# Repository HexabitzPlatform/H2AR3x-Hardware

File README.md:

# H2AR3x-Hardware
Hexabitz AC Current and Voltage Sensor Module Hardware Design

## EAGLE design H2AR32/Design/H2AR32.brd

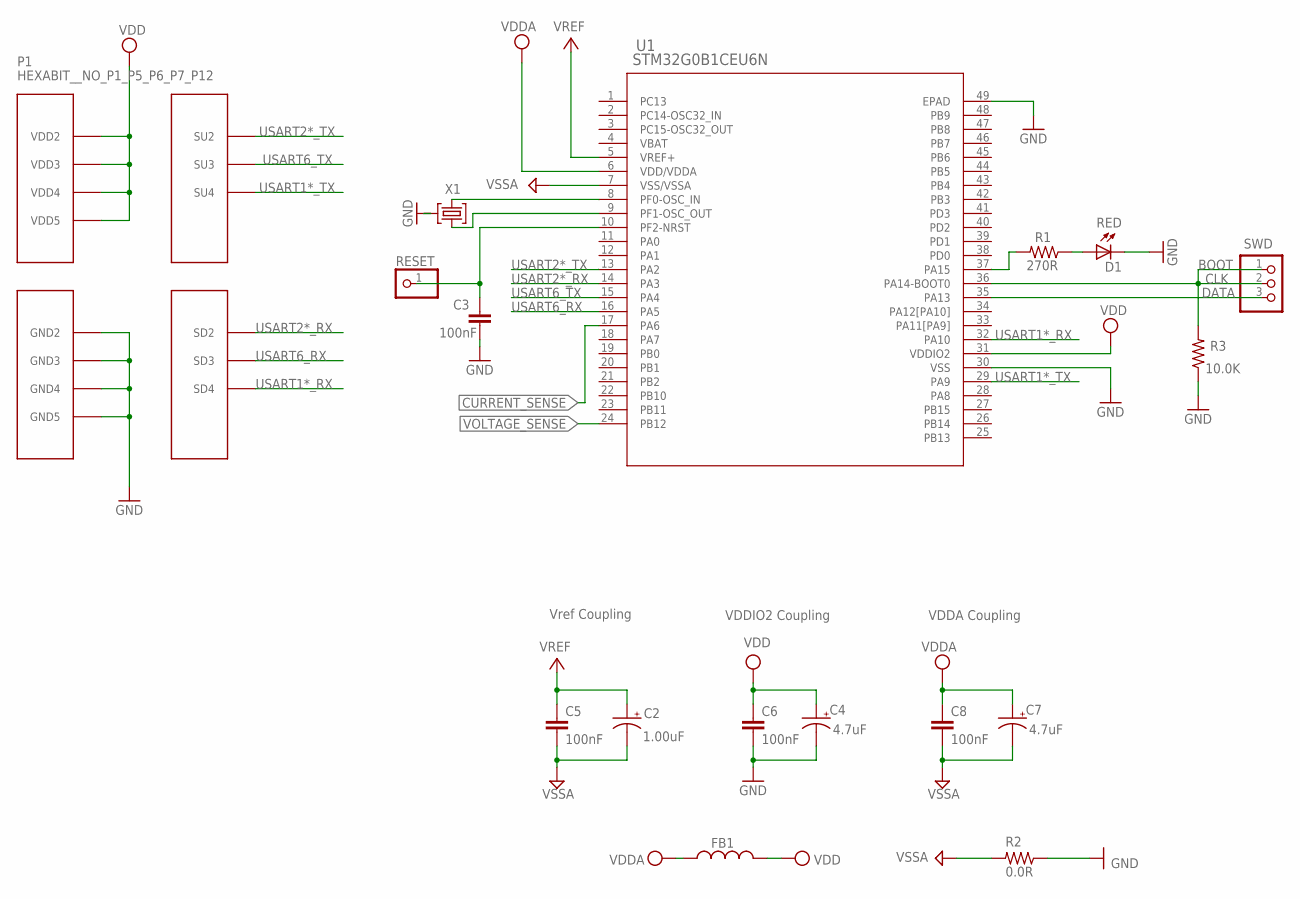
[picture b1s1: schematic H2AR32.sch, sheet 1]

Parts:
C2: 1.00uF; C-0805-POL; TOLERANCE 10%; VOLTAGE_RATING 16V; MPN CC0805KKX7R7BB105
C3, C5, C6: 100nF; C-0603; TOLERANCE 10%; VOLTAGE_RATING 10V; MPN C0603C104K8RACTU
C4, C7: 4.7uF; C-0805-POL; TOLERANCE 10%; VOLTAGE_RATING 25V; MPN GRM21BC81E475KA12L
C8: 100nF; C-0603; TOLERANCE 10%; VOLTAGE_RATING 10; MPN C0603C104K8RACTU
D1: RED; VLMS1300-GS08; MPN VLMS1300-GS08
FB1: FB-TDK_MMZ1608Y300B; MPN MMZ1608Y300B
P1: HEXABIT__NO_P1_P5_P6_P7_P12; HEXABIT_17.32_NO_P1_P6_P5_P7_P12
R1: 270R; R-0603; TOLERANCE 5%; MPN RC0603FR-07270RL
R2: 0.0R; R-0603; MPN RC0603JR-070RL
R3: 10.0K; R-0603; TOLERANCE 5%; MPN RC0603JR-0710KL
RESET: R; 1X01
SWD: PINHD-1X3; 1X03
U1: STM32G0B1CEU6N; HEXABITZ_ICS_QFN_B1CEU6_STM-L
X1: XTALL_CSTCE8M00G52

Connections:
CLK: R3.2, SWD.1, SWD.2, U1.36 (PA14-BOOT0)
CURRENT_SENSE: U1.17 (PA6); also elsewhere on the board
DATA: SWD.3, U1.35 (PA13)
GND: C3.2, C4.2 (-), C6.2, D1.C, P1.PAD_PD8 (GND2), P1.PAD_PD9 (GND3), P1.PAD_PD10 (GND4), P1.PAD_PD11 (GND5), R2.1, R3.1, U1.30 (VSS), U1.49 (EPAD), X1.P$2 (2)
unnamed: R1.2, U1.37 (PA15)
unnamed: D1.A, R1.1
unnamed: U1.8 (PF0-OSC_IN), X1.P$1 (1)
unnamed: U1.9 (PF1-OSC_OUT), X1.P$3 (3)
unnamed: C3.1, RESET.1, U1.10 (PF2-NRST)
USART1*_RX: P1.PAD_PD4 (SD4), U1.32 (PA10)
USART1*_TX: P1.PAD_PU4 (SU4), U1.29 (PA9)
USART2*_RX: P1.PAD_PD2 (SD2), U1.14 (PA3)
USART2*_TX: P1.PAD_PU2 (SU2), U1.13 (PA2)
USART6_RX: P1.PAD_PD3 (SD3), U1.16 (PA5)
USART6_TX: P1.PAD_PU3 (SU3), U1.15 (PA4)
VBAT: U1.4 (VBAT)
VDD: C4.1 (+), C6.1, FB1.2, P1.PAD_PU8 (VDD2), P1.PAD_PU9 (VDD3), P1.PAD_PU10 (VDD4), P1.PAD_PU11 (VDD5), U1.31 (VDDIO2)
VDDA: C7.1 (+), C8.1, FB1.1, U1.6 (VDD/VDDA); also elsewhere on the board
VOLTAGE_SENSE: U1.24 (PB12); also elsewhere on the board
VREF: C2.1 (+), C5.1, U1.5 (VREF+); also elsewhere on the board
VSSA: C2.2 (-), C5.2, C7.2 (-), C8.2, R2.2, U1.7 (VSS/VSSA); also elsewhere on the board

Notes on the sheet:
VDDA Coupling
VDDIO2 Coupling
BOOT
Vref Coupling

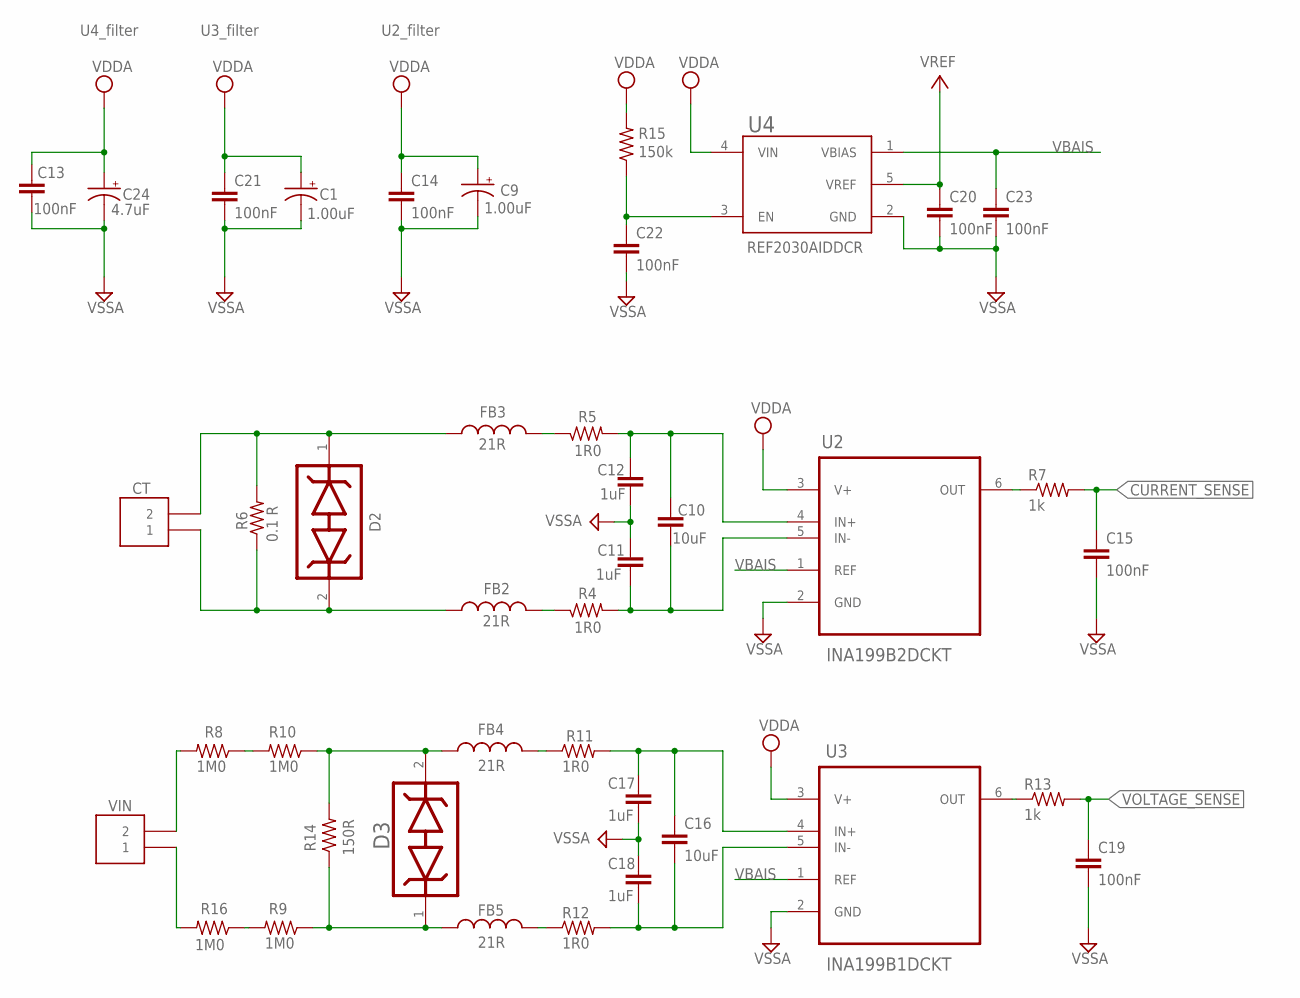
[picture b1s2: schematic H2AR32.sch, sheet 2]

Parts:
C1, C9: 1.00uF; C-0805-POL; TOLERANCE 10%; VOLTAGE_RATING 16V; MPN CC0805KKX7R7BB105
C10: 10uF; C-0603; VOLTAGE_RATING 6.3v; MPN C0603C106M9PACTU
C11, C12, C17, C18: 1uF; C-0603; TOLERANCE 10%; VOLTAGE_RATING 10v; MPN C0603C105K8RACTU
C13, C14, C15, C19, C20, C21, C22, C23: 100nF; C-0603; TOLERANCE 10%; VOLTAGE_RATING 10V; MPN C0603C104K8RACTU
C16: 10uF; C-0603; TOLERANCE 20%; VOLTAGE_RATING 6.3V; MPN C0603C106M9PACTU
C24: 4.7uF; C-0805-POL; TOLERANCE 10%; VOLTAGE_RATING 25V; MPN GRM21BC81E475KA12L
CT: 1546111-2
D2, D3: BOURNS_CDSOD323-T03SCBOURNS_CDSOD323-T03SC_0_0; BOURNS_CDSOD323-T03SC_0
FB2, FB3, FB4, FB5: 21R; FB-0805; MPN FBMJ2125HM210NT
R4, R5, R11, R12: 1R0; R-0603; TOLERANCE 1%; MPN CRCW06031R00FKEA
R6: 0.1 R; R2512
R7, R13: 1k; R-0603; TOLERANCE 5%; MPN RC0603JR-071KL
R8, R9, R10, R16: 1M0; R1206; MPN RT1206BRD071ML
R14: 150R; R1206; MPN ERA-8AEB151V
R15: 150k; R-0603; TOLERANCE 1%; MPN CRCW0603150KFKEA
U2: INA199B2DCKT; SOT65P210X110-6N
U3: INA199B1DCKT; SOT65P210X110-6N
U4: TEXAS_INSTRUMENTS_REF2033AIDDCRTEXAS_INSTRUMENTS_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; TEXAS_INSTRUMENTS_REF2033AIDDCR_2; MPN REF2030AIDDCR
VIN: 1546111-2

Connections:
CT_3: CT.1, D2.2, FB2.2, R6.1
CT_4: CT.2, D2.1, FB3.2, R6.2
CURRENT_SENSE: C15.1, R7.2; also elsewhere on the board
unnamed: C10.1, C11.2, R4.2, U2.5 (IN-)
unnamed: FB2.1, R4.1
unnamed: C10.2, C12.1, R5.2, U2.4 (IN+)
unnamed: FB3.1, R5.1
unnamed: R9.2, R16.1
unnamed: R8.2, VIN.2
unnamed: R8.1, R10.2
unnamed: R16.2, VIN.1
unnamed: R7.1, U2.6 (OUT)
unnamed: C22.1, R15.1, U4.3 (EN)
unnamed: C16.1, C17.2, R11.2, U3.4 (IN+)
unnamed: C16.2, C18.1, R12.2, U3.5 (IN-)
unnamed: FB4.2, R11.1
unnamed: FB5.2, R12.1
unnamed: D3.2, FB4.1, R10.1, R14.2
unnamed: D3.1, FB5.1, R9.1, R14.1
unnamed: R13.1, U3.6 (OUT)
VBAIS: C23.1, U2.1 (REF), U3.1 (REF), U4.1 (VBIAS)
VDDA: C1.1 (+), C9.1 (+), C13.1, C14.1, C21.1, C24.1 (+), R15.2, U2.3 (V+), U3.3 (V+), U4.4 (VIN); also elsewhere on the board
VOLTAGE_SENSE: C19.1, R13.2; also elsewhere on the board
VREF: C20.1, U4.5 (VREF); also elsewhere on the board
VSSA: C1.2 (-), C9.2 (-), C11.1, C12.2, C13.2, C14.2, C15.2, C17.1, C18.2, C19.2, C20.2, C21.2, C22.2, C23.2, C24.2 (-), U2.2 (GND), U3.2 (GND), U4.2 (GND); also elsewhere on the board

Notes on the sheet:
U2_filter
U3_filter
U4_filter

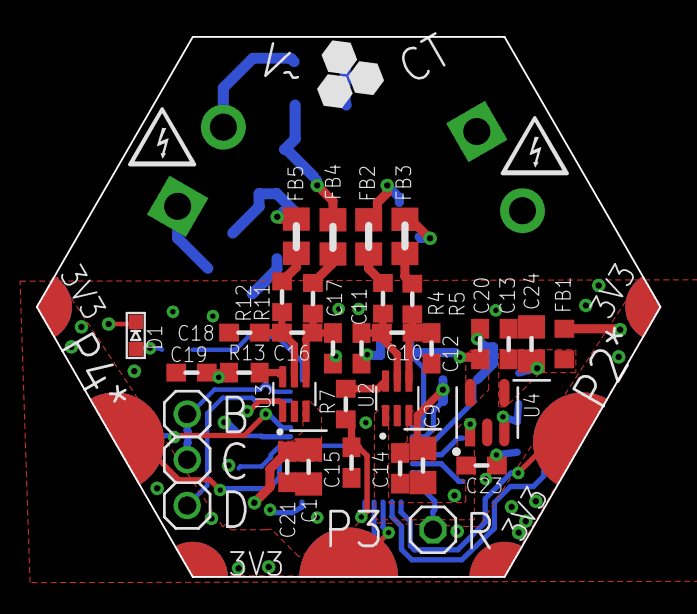
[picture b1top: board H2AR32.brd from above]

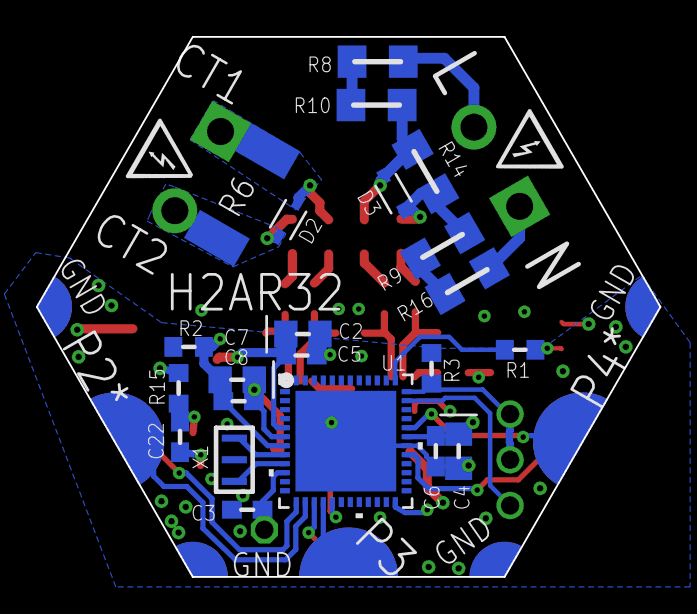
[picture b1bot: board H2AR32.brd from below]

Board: 4 copper layers, 34.6 x 30.0 mm, 58 parts (22 on the bottom side), 40 nets.

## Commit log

2020-05-26 finish schematic Un-checked attributes not finished
2020-05-27 some bugs fixed
2020-05-28 some fixes
2020-06-06 finished BOM
2020-06-07 no message
2020-06-12 Final Design: High voltage logos were added High voltage clearance checked * were added to boot pins 100A & 4A (optional ) CTs were added to BOM ERC & DRC were made
2020-06-19 re-order the ports
2021-04-19 final with double check
2021-04-19 rev1 change
2023-09-26 -Changing the MCU to stm32g0b1ceu6n -Improving the layout design for better performance -Adding extra capacitors to the amplifiers supply
2023-09-26 -Update BOM
2023-11-12 -Update the pcb layout design to be based on 4 layers for better performance and improve the analog design

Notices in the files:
parts and their libraries:
HEXABITZ_ICs: COPYRIGHT: Copyright (C) 2022 Ultra Librarian. All rights reserved.
